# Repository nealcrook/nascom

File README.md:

# NASCOM

Software, utilities and documentation for the Z80-based NASCOM computers.

* PolyDos - code and documentaton for this excellent NASCOM operating-system
* ROM - NASCOM ROM images (monitors etc), most including source code
* converters - scripts for manipulating NASCOM disk and binary images
* doc
  * NASCOM 1 RAM expansion (tested) -- see nascom1_expansion for PCB
  * NASCOM 2 RAM expansion (untested)
  * NASCOM Keyboard -- waveforms and description of the software-scanned keyboard
  * NASCOM UART performance -- an attempt to understand the (speed) limitations of the NASCOM UART
* gm808_eprom_programmer - code, photos and documentation for this 2708/2716 EPROM programmer
* hw_sim - verilog simulation of the NASCOM 1 and NASCOM 2 video sub-systems
* m5 - a very simple "high-level language"
* nascom 4 - a NASCOM re-imagined for the 21st-century FPGA age
* programs - miscellaneous code
* nascom_kbd - Uses a Raspberry Pi Pico to interface a PS/2 keyboard to the NASCOM
* sdcard - Arduino-based SDcard storage. There are 2 versions:
  * A version that connects to the serial port instead of a tape recorder, and works with NAS-SYS tape commands
  * A version that connects to the PIO, with all supporting software to run PolyDos and to extract data from your old floppies
  * NEW: a PCB and a detailed user guide
* nascom1_expansion - a 100mm x 100mm PCB that breaks into pieces to provide sdcard, RAM card and connector adaptors

## Projects in planning

At the concept stage..

* Get NASCOM CP/M running on a NASCOM 2 without the need for a special NASMD PROM

## Comments/improvements

* Email me or use the 'issues' button at the top on the github page.

* Fork the project and make a merge request

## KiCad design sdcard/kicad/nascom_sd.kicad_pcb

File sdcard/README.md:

# NASdsk and NAScas

This is a project to provide SDcard-based storage for a NASCOM. It has been
tested on NASCOM 1 and NASCOM 2 computers running NAS-SYS monitors.

The hardware is cheap and simple and basically consists of an Arduino and an
SDcard adaptor. A PCB is available but it's equally feasible to build a
hand-wired unit using protoype cards.

* NASdsk - Arduino sketch. This design connects to the NASCOM PIO and uses a custom EPROM
on the NASCOM. It allows the PolyDos operating system to boot and run using virtual disk images stored on SDcard.

* NAScas - Arduino sketch. This design connects to the (digital side of the) NASCOM tape
interface. It acts as a "digital tape-recorder" allowing the existing read and write commands to store data on SDcard instead of audio tape. No modifications or EPROMs are required on the NASCOM.

* sd_merged - Arduino sketch. This design superceeds NASdsk and NAScas by combining both sets of
functionality into a single image.

* setup - Arduino sketch. Run this once on the hardware to program the profile record into EEPROM.

Other stuff here:

* doc -- a full user-guide, construction notes, schematics, details of the protocols and command-sets.

* photos -- photos of the PCB and of the prototype units. Screenshots of the software running on my NASCOM 2.

* host_programs -- z80 software related to these two projects, including
software for "scraping" a floppy disk into a binary virtual disk image.

* kicad -- the kicad database for the schematic and PCB.

Relevant stuff elsewhere:

../converters has software for converting files between various formats,
including NASCOM-related audio and digital formats. It also contains a tool for
manipulating PolyDos disk images.

## EPROM programming service

If anyone is looking to build a nascom_sdcard and has an EPROM that they need
erasing and programming, I will be happy to do this on a cost-of-postage
basis. Contact me to make arrangements.

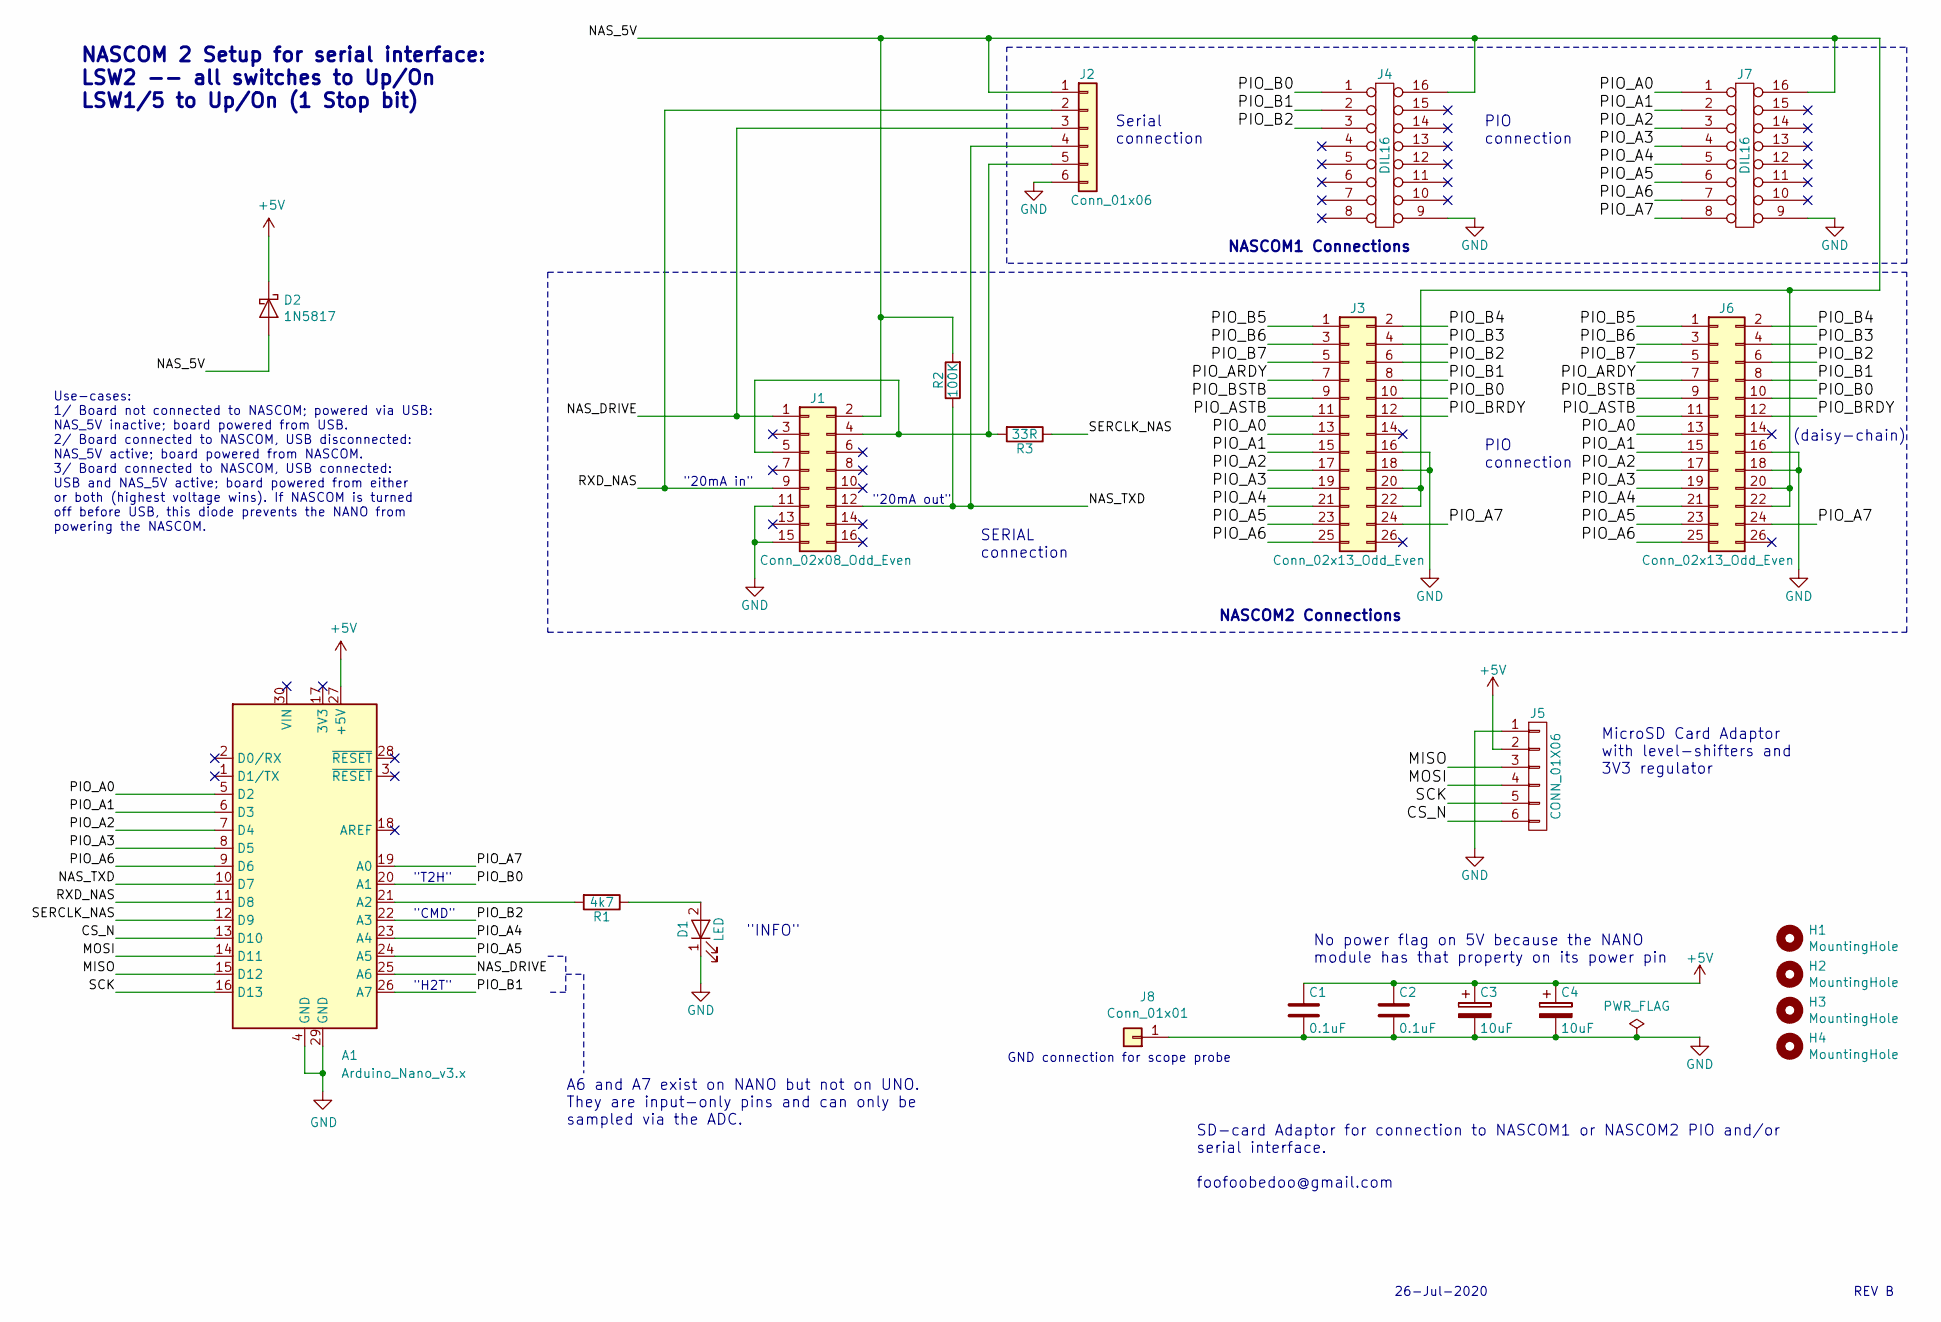
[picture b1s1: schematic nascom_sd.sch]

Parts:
A1: Arduino_Nano_v3.x; Arduino_Nano
C1, C2: 0.1uF; C_Axial_L3.8mm_D2.6mm_P7.50mm_Horizontal
C3, C4: 10uF; C_Axial_L5.1mm_D3.1mm_P10.00mm_Horizontal
D1: LED; LED_D5.0mm
D2: 1N5817; D_DO-41_SOD81_P10.16mm_Horizontal
H1, H2, H3, H4: MountingHole; MountingHole_3.2mm_M3
J1: Conn_02x08_Odd_Even; IDC-Header_2x08_P2.54mm_Vertical
J2: Conn_01x06; PinHeader_1x06_P2.54mm_Vertical
J3, J6: Conn_02x13_Odd_Even; IDC-Header_2x13_P2.54mm_Vertical
J4, J7: DIL16; DIP-16_W7.62mm_Socket
J5: CONN_01X06; SDcard_module_1x06_P2.54mm
J8: Conn_01x01; Pin_D1.0mm_L10.0mm
R1: 4k7; R_Axial_DIN0204_L3.6mm_D1.6mm_P7.62mm_Horizontal
R2: 100K; R_Axial_DIN0204_L3.6mm_D1.6mm_P7.62mm_Horizontal
R3: 33R; R_Axial_DIN0204_L3.6mm_D1.6mm_P7.62mm_Horizontal

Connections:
+5V: A1.27 (+5V), C1.1, C2.1, C3.1, C4.1, D2.1 (K), J5.2
/CS_N: A1.13 (D10), J5.6
/MISO: A1.15 (D12), J5.3
/MOSI: A1.14 (D11), J5.4
/NAS_5V: D2.2 (A), J1.2, J2.1, J3.20, J3.22, J4.16, J6.20, J6.22, J7.16, R2.2
/NAS_DRIVE: A1.25 (A6), J1.1, J2.3
/NAS_TXD: A1.10 (D7), J1.12, J2.4, R2.1
/PIO_A0: A1.5 (D2), J3.13, J6.13, J7.1
/PIO_A1: A1.6 (D3), J3.15, J6.15, J7.2
/PIO_A2: A1.7 (D4), J3.17, J6.17, J7.3
/PIO_A3: A1.8 (D5), J3.19, J6.19, J7.4
/PIO_A4: A1.23 (A4), J3.21, J6.21, J7.5
/PIO_A5: A1.24 (A5), J3.23, J6.23, J7.6
/PIO_A6: A1.9 (D6), J3.25, J6.25, J7.7
/PIO_A7: A1.19 (A0), J3.24, J6.24, J7.8
/PIO_ARDY: J3.7, J6.7
/PIO_ASTB: J3.11, J6.11
/PIO_B0: A1.20 (A1), J3.10, J4.1, J6.10
/PIO_B1: A1.26 (A7), J3.8, J4.2, J6.8
/PIO_B2: A1.22 (A3), J3.6, J4.3, J6.6
/PIO_B3: J3.4, J6.4
/PIO_B4: J3.2, J6.2
/PIO_B5: J3.1, J6.1
/PIO_B6: J3.3, J6.3
/PIO_B7: J3.5, J6.5
/PIO_BRDY: J3.12, J6.12
/PIO_BSTB: J3.9, J6.9
/RXD_NAS: A1.11 (D8), J1.9, J2.2
/SCK: A1.16 (D13), J5.5
/SERCLK_NAS: A1.12 (D9), R3.1
GND: A1.4 (GND), A1.29 (GND), C1.2, C2.2, C3.2, C4.2, D1.1 (K), J1.11, J1.15, J2.6, J3.16, J3.18, J4.9, J5.1, J6.16, J6.18, J7.9, J8.1
unnamed: A1.21 (A2), R1.2
unnamed: D1.2 (A), R1.1
unnamed: J1.4, J1.5, J2.5, R3.2

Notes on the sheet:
NASCOM1 Connections
PIO connection
MicroSD Card Adaptor with level-shifters and 3V3 regulator
SD-card Adaptor for connection to NASCOM1 or NASCOM2 PIO and/or serial interface. foofoobedoo@gmail.com
"INFO"
SERIAL connection
"20mA out"
"20mA in"
(daisy-chain)
Serial connection
"CMD"
"T2H"
"H2T"
NASCOM2 Connections
26-Jul-2020
No power flag on 5V because the NANO module has that property on its power pin
NASCOM 2 Setup for serial interface: LSW2 -- all switches to Up/On LSW1/5 to Up/On (1 Stop bit)
REV B
A6 and A7 exist on NANO but not on UNO. They are input-only pins and can only be sampled via the ADC.
Use-cases: 1/ Board not connected to NASCOM; powered via USB: NAS_5V inactive; board powered from USB. 2/ Board connected to NASCOM, USB disconnected: NAS_5V active; board powered from NASCOM. 3/ Board connected to NASCOM, USB connected: USB and NAS_5V active; board powered from either or both (hig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
GND connection for scope probe

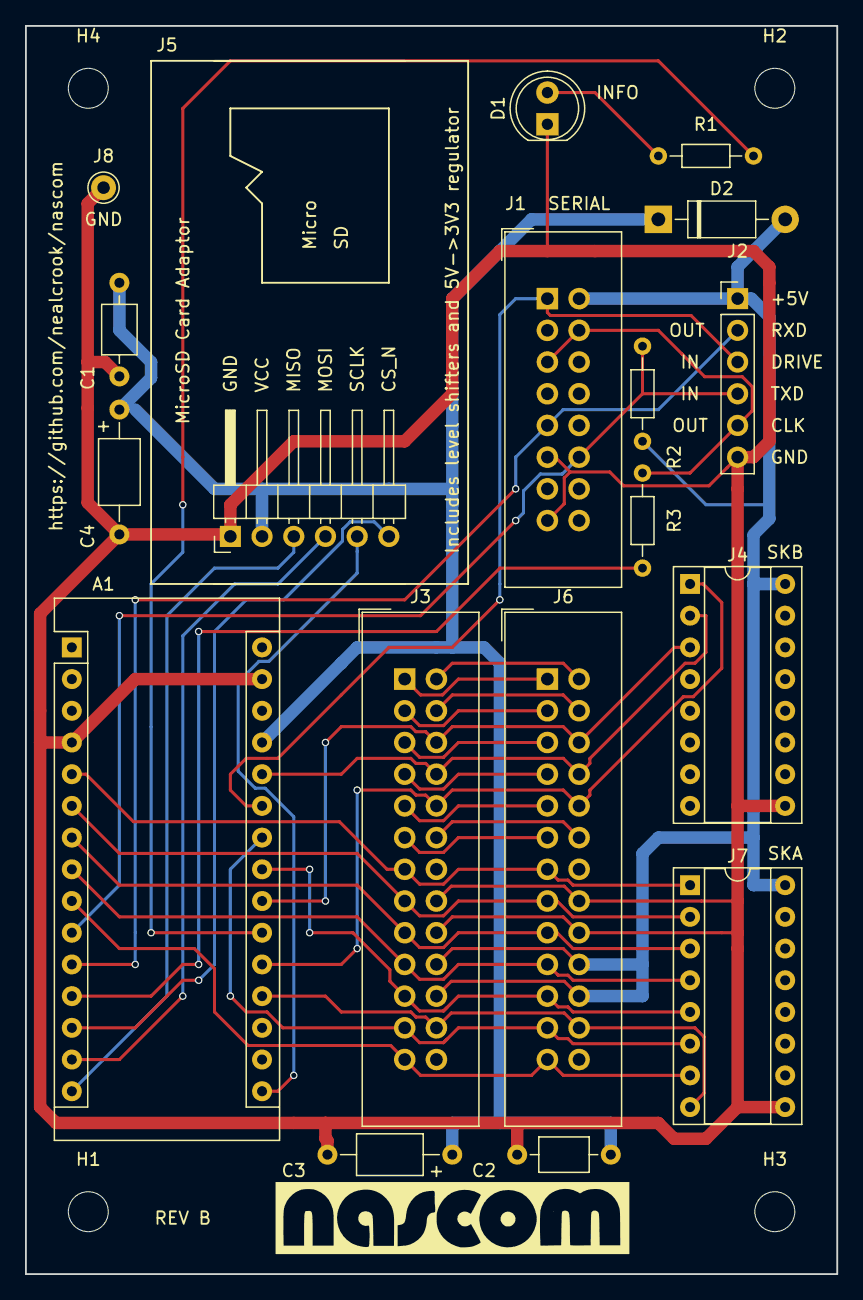
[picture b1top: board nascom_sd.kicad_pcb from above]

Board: 2 copper layers, 65.0 x 100.0 mm, 22 parts (0 on the bottom side), 34 nets.

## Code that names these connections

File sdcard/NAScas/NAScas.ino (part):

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//
// Name   Direction   ARDUINO   NASCOM 2
// ---------------------------------------------------------------
// NAS_DRIVE  IN       ANA6     pin 1       DRIVE OUT
// NAS_TXD    IN       DIG7     pin 12      20mA OUT
// RXD_NAS    OUT      DIG8     pin 9       20mA IN
// SERCLK_NAS OUT      DIG9     pin 4 & 5   EXT TX CLK, EXT RX CLK
// GND                          pin 11 & 15 GND
// 5V                           pin 2       5V   (NOTE)
//
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
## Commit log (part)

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2018-09-06 Add new disk images from my floppy disk scrapes.
2018-09-07 Add new disk containing ASTROTRAPS
2018-09-07 Update README.md
    Update current status.
2018-09-11 Add sdoff.asm source and description.
2018-09-14 Update README.md
    Add description of nascon. nas2cas and cas2nas are now obsolete.
2018-10-18 Convert a binary file to a C data structure for embedding into a C program.
2018-10-19 Make output go to the serial port rather than the screen.
2018-11-16 fix bug in self-relocating command.
2019-04-16 Tidy up files associated with NASCOM1 video simulation.
2019-04-18 Directory now works for all 3 filesystems Read now works for Flash and finds the correct dirent for vdisk ..running out of space tho, so had to reduce the scope of the virtual flash filesystem (boo h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
2019-04-22 remove some debug messages. tidy up comments, particularly at start. implement optional AI qualifier for auto-increment of filenames.
2019-04-25 Add Erase command for SDcard files Rename to NASCAS and import new serboot code with modified prompt Re-fix a couple of formatting issues that I lost from my previous edit.
2019-04-27 NASCAS -> NAScas
2019-04-27 Expand
2019-04-28 Add photos
2019-05-09 Error detection on writes, and report errors to NASCOM screen instead of to the debug console.
2019-05-14 Linewrap the comments and tidy up some of the sytax around the use of unions and function pointers.
2019-08-30 No functional change. Change signal naming to match PCB. Various updates to header comments, including a reference to baud speed experiments document.
2019-09-01 note dependence on SdFat and describe configuration needed for the code to fit
2019-10-05 Update pinout to match PCB. Change code to accommodate analogue read of pin A7
2019-10-09 Fix typos. Add descriptions of ROM routines
2019-10-13 Memory expansion projects for the NASCOM 1 and 2.
2019-10-16 Add NASCOM ROM images
2019-10-18 move UART document from NAScas to docs area
2019-11-09 BUG: in NAScas the "DV" (drectory of virtual disk) the number of directory entries was calculated wrongly and so the directory listing went on "forever" listing loads of junk beyond the end of the tr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
2020-02-01 Fix bugs associated with loading BASIC programs from virtual disk: 1/ ignore "auto-go" flag when loading programs to 0x10D6 2/ add 2 NULs after the file-name header; without this, the first block of 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
2020-02-02 Implement create command. Delete some subroutines that will not be needed.
2020-02-02 undelete command was not as simple as I thought.. it went wrong for some useful wildcard cases. It's working now, and the effect of the bugfix was to refactor some code to create &names_ref() and sim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
2020-02-09 Add NASCOM_keyboard document.
2020-03-01 Previously, the importer would only match filenames in the host filesystem that were legal PolyDos names. That's not what the documentation (that I wrote) says - it should recognise eg a .NAS file an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
2020-03-12 Add circuit schematics. Update README.
2020-03-22 Converted from awk to PERL using a2p
2020-03-22 Add translation of 8080 op-codes SUB SBB
2020-03-26 Bug-fix. Previously, if a file was referenced with a relative path its extension would not get extracted correctly and so it was necessary to use the -in and/or -out switches to set the format explic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
2020-03-29 The original disk image seemed to have a corruption in its header information; it referred to an additional disk entry that did not exist. Repaired the header, using the 'repair' command of polydos_v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
2020-04-11 Fix typos.
2020-04-13 Fix one more B->3 ambiguity in the hex dump, which made an INC HL into a DEC HL and stopped variables from working properly (they were fetched correctly but were stored byte-swapped at an out-by-1 ad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
2020-04-18 Modified source to build easily for T2/T4 or for NAS-SYS
2020-04-19 Cleaned up versions for NASBUG and NAS-SYS, with build script and updated documentation.
2020-04-27 All components modelled enough. Removed several transcrition errors from the netlist. The main dividers and clocks are now initialising and counting.
2020-05-09 Describe CPU access
2020-05-14 Revise status
2020-05-19 Add write command and note about MSDOS 8.3 filenames.
2020-05-22 Now have separate sections describing SDcard setup for NAScas and nascom_sdcard, making things clearer, I hope.
2020-05-23 Add -pad8 -pad256 commands to round-up image sizes.
2020-06-02 Bump NAScas to version 1.2 Add new #define CONSOLE to build new serial interface for control from a PC Add new #defines for each image that can be in the Flash, so that they can be individually inclu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
2020-06-03 Configure for NASCOM2 by default Fix up comments/examples in parser
2020-06-05 Tidy up comments (tidy-up) Remove CMD_DEFAULT (turned out not to be useful) Remove illegal FID values from case statement and remove fid() function. Remove STATE_FILE (unused) Start of support for di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
2020-06-07 Add command to write default profile record to EEPROM. Will be used by the merged NAScas/nascom_sdcard environment.
2020-06-07 Experimental merge of NAScas and nascom_sdcard Comments and code ordering need tidy-up.
2020-06-14 Reorganise: move doc to the top-level; move photos to a single directory and rename to avoid clashes.
2020-06-14 Two small but significant architectural changes: 1/ Previously, the code would block in loop() waiting for a command. Now, it can check for a command in a non-blocking way. This allows it to be used 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
2020-06-15 move protocol description into separate document, in markdown format.
2020-06-16 remove material that's been moved elsewhere, to avoid duplication.
2020-06-19 Re-organise misc programs into a separate directory. Assorted clean-ups to documentation.
2020-06-20 Fix link.
2020-06-20 Fix attributes on some BASIC files, and update disk index. Change attrib command in polydos_vfs so that the arguments match the order in PolyDos command (which also matches the order in the directory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
2020-06-21 Fix typos and markdown formatting.
2020-07-14 add some casts to be sure to avoid arithmetic truncation change cmd_seek to always fetch its args even if the disk is non-existent; should make the protocol more rugged.
2020-07-16 Revamped version of SDBOOT.asm - much cleaner and more useful. Revised documentation accordingly. Added pre-built disk image based on new SDBOOT core. Other documentation tweaks.
2020-07-30 Rename nascom_sdcard sketch Add new setup sketch revise README files accordingly.
2020-07-30 Revamp to cover merged software.
2020-07-31 Use setup and defines from common files. Binaries checked and seen to be identical.
2020-07-31 fix typo in dskboot invocation.
2020-08-31 Tweak assembly details: revise resistor values and add CPC part numbers for some parts.
2020-08-31 move code out of ISR.
2020-09-02 Add table of contents.
2020-12-24 Revise profiles to reflect addition of write-protect register and to change memory mapping port from 3 to 18.
2021-01-30 NAS-SYS3 source and bin and rebuild flow
2021-02-07 Add notes on rebuild of T2 from source.
2021-02-08 whitespace cleanup, use some defines for character codes, first round of comments/cleanup
2021-02-09 lots of formatting tidyup
2021-02-10 NASSYS1 source
2021-02-17 Tidy up some comments in serboot.asm - including making it clear that this version is for NAS-SYS. Create a new version, serbootT4, which is currently untested.
2021-03-02 change paths to suit new location of this script.
2021-03-27 Updates after build of 1st PCB; add new registers, describe I/O bus, fix minor errors and inconsistencies in construction section.
2021-04-11 Add nascom_sdcard version of NASDOS ROM image.
2021-04-11 Swap MAP80 VFC video select port EE/EF
2021-04-18 Swapped ports EE/EF back after getting CP/M to boot and realising that the CP/M 2.2 code relied on the other assignment. Documented some of the gory details. Added notes on connecting a disk drive. M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
2021-04-21 Make local SDcard version of PolyDos work with 16 disk from SDcard. First 4 assigned initially to drives 0-3.
2021-05-02 fix comments and code error. This version shown to create bit-exact disk copy.
2021-05-23 First working version of setdrv utility. Revise documentation.
2021-06-29 New version of nascom_sdcard firmware for NASBUG T4. Aims to fix bugs reported by Trevor. New version also adds some images to the internal file-system, for ZEAP 1.1 and for M5.
2021-07-25 First notes on BIOS work/debug
2021-07-31 Next steps on SDcard support: the equates are in place and I can support a number of disks that have the correct geometry for the SDcard but whic hare actually implemented via the floppy disk control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
2021-09-06 Accesses (one) virtual drive on SDcard, correctly. Revise documentation in README.md to suit and to explain problems encountered.
2021-09-11 Fix paths in readme and make .gitignore complete.
2021-09-14 Add SDMOUNT utility
2021-09-16 warm.com does a CP/M warm start; can be used as a "NOP" in a submit script
2021-09-18 commit the correct version this time
2021-09-30 Add new tool sdcard_editor for manipulating the SDcard image. Renamed make_sdcard_image to make_rom_menu
2021-10-02 Stand-alone boot-loader for starting CP/M from SDcard.
2021-10-04 Tidy up tools scripts and add some instructions
2021-10-04 Remove individual disk images; these are now part of the SDcard image and can be inserted/extracted at will using sdcard_editor.
2021-10-05 bug in sdcard_editor: failed to seek to end of file before adding padding, leading to image corruption. Fixed that, and updated the reference image.
2021-10-07 First working version!
2021-11-12 Describe REV C PCB.
2021-11-21 Revise handbook to describe software programmable character generator.
2022-03-09 ZEN for NASCOM T4 or NAS-SYS monitors.
2022-03-20 Mention toZ80 and tidy up some references and links. Add page on polydos_vfs help.
2022-03-21 More comments annotated.
2022-03-28 More source comment annotation. Script to convert from ZEAP format.
2022-04-18 Update README.md
    Add new youtube videos. Various other tweaks
2022-05-29 Add more images.
2022-06-03 Add complete T4 manual that includes source code. Revise readme to cross-reference both versions of the documentation.
2022-06-20 Source code for RP/M
2022-06-23 Comments around keyboard routines
2022-06-26 decoded vectored i/o
2022-07-11 Redo simon5 with full binary instead of only the first 2Kbytes.
2022-08-28 No functional/code change; improve comments.
2022-08-29 Latest version, in sd_merged, loads and starts SDBOOT bootstrap code at 0D00 rather than 1000, allowing images to be loaded at 1000.
2022-10-04 Add code to test PIO connection
2022-10-19 Fix some bugs in SDBOOT0.asm, add more images, improve the comments. Make the code load at $d00 instead of $1000, so that it can load images at $1000.
2022-10-22 Revise manual to describe REV C-NAS1 PCB and to describe latest versions of dskboot and util ROM.
2022-11-15 Add PolyTest manual and update README.md accordingly
2022-11-19 Add disassembly of SIMON4.4
2022-11-21 Add example .wav file for wav2bin
2022-12-03 Updates for REV B PCB. Refer to new FPGA release, Rev1.3
2023-01-04 Lollipop lady trainer somewhat disassembled.
2023-02-19 Add new simon versions, update README
2023-02-21 Add disassembled simon43. Tweak simon42 source. Update docs and rebuild script to include simon43.
2023-08-04 fix bug in setdrv where drives A-F were wrongly reported as K-O.
2023-09-20 Fix bug reported by Bob; tool did not work correctly under Windows (Strawberry PERL). Fix is to call "binmode" on each file handle as it is opened.
2023-12-23 Disassembly of Movement Computer Systems drum machine ROMs.
2023-12-26 latest updates
2023-12-28 More disassembly; detected the character set. Hand-edited source with more comments. Script to rebuild from source and check against the golden ROM.
2023-12-31 Reformat, correct errors, more details.
2024-02-08 Tweaks to the handbook: add reference designators to the IC sockets in the parts list and correct the count of sockets per stage. Tidy up the notes about the pulldown needed to prevent spurious input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
2024-05-30 Add source code
2024-11-06 revise README for PolyDos 4
2024-11-07 Add PolyDos4 disk image; update descriptions.
2025-06-23 Update documentation list Cross-reference keyboard document from nascom_kbd section
2025-10-27 revise FPGA image list: convert to table and add 1.4
